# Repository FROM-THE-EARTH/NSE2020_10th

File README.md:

# NSE2020_10th
能代2020の10期ロケット用電装

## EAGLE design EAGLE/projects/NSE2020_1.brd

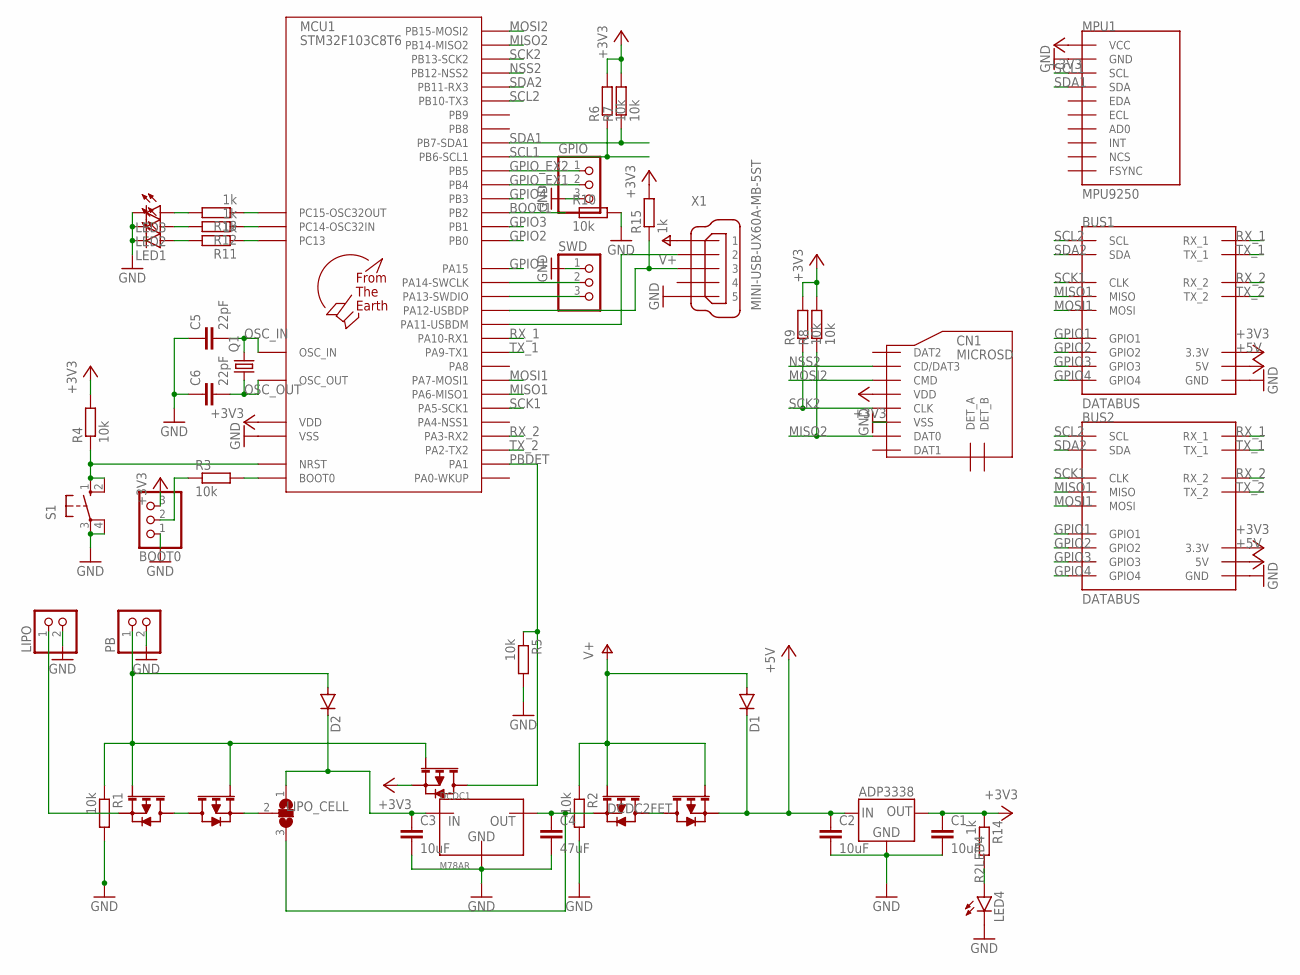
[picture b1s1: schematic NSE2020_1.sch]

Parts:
BOOT0: PINHD-1X3; 1X03
BUS1, BUS2: DATABUS; 8X2
C1, C2, C3: 10uF; C2012
C4: 47uF; C2012
C5, C6: 22pF; C2012
CN1: MICROSD; DM3AT
D1, D2: DIODE-SOD123; SOD123
DCDC1: M78AR
FET1, FET2, FET3, FET4, FET5: 2SJ681
GPIO: PINHD-1X3; 1X03
IC1: ADP3338-3.3; SOT-223
LED1, LED2, LED3, LED4: LEDSML0805; SML0805
LIPO: PINHD-1X2; 1X02
LIPO_CELL: SJ2W; SJ_2
MCU1: STM32F103C8T6; LQFP48
MPU1: MPU9250; GY-9250
PB: PINHD-1X2; 1X02
Q1: CRYSTALHC49S; HC49/S
R1, R2, R3, R4, R5, R6, R7, R8, R9, R10: 10k; M2012
R11, R12, R13, R14, R15: 1k; M2012
S1: 10-XX; B3F-10XX
SWD: PINHD-1X3; 1X03
U$1: F.T.E.LOGO; LOGO
X1: MINI-USB-UX60A-MB-5ST; UX60A-MB-5ST

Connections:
+3V3: BOOT0.3, BUS1.P6 (3.3V), BUS2.P6 (3.3V), C1.1, CN1.VDD, FET5.P$3, IC1.1 (OUT), IC1.2 (OUT), MCU1.1 (VDD), MCU1.9 (VDD), MCU1.24 (VDD), MCU1.36 (VDD), MCU1.48 (VDD), MPU1.P1 (VCC), R4.2, R6.2, R7.2, R8.2, R9.2, R14.1, R15.2
+5V: BUS1.P7 (5V), BUS2.P7 (5V), C2.1, D1.C, FET4.P$3, IC1.3 (IN)
BAT2DCDC: C3.1, D2.C, DCDC1.P1 (IN), LIPO_CELL.1
BOOT0: BOOT0.2, R3.1
BOOT0_R: MCU1.44 (BOOT0), R3.2
BOOT1: MCU1.20 (PB2), R10.1
DCDC2FET: C4.1, DCDC1.P3 (OUT), FET3.P$3, LIPO_CELL.3
DM: MCU1.32 (PA11-USBDM), X1.2
DP: MCU1.33 (PA12-USBDP), R15.1, X1.3
FET2FET: FET3.P$2, FET3.P$4, FET4.P$2, FET4.P$4
FET2JUMP: FET2.P$3, LIPO_CELL.2
GND: BOOT0.1, BUS1.P11 (GND), BUS2.P11 (GND), C1.2, C2.2, C3.2, C4.2, C5.1, C6.1, CN1.VSS, DCDC1.P2 (GND), GPIO.3, IC1.4 (GND), LED1.C, LED2.C, LED3.C, LED4.C, LIPO.2, MCU1.8 (VSS), MCU1.23 (VSS), MCU1.35 (VSS), MCU1.47 (VSS), MPU1.P2 (GND), PB.2, R1.2, R2.2, R5.2, R10.2, S1.3, S1.4 (P1), SWD.1, X1.5
GPIO1: BUS1.P3 (GPIO1), BUS2.P3 (GPIO1), MCU1.38 (PA15)
GPIO2: BUS1.P10 (GPIO2), BUS2.P10 (GPIO2), MCU1.18 (PB0)
GPIO3: BUS1.P14 (GPIO3), BUS2.P14 (GPIO3), MCU1.19 (PB1)
GPIO4: BUS1.P15 (GPIO4), BUS2.P15 (GPIO4), MCU1.39 (PB3)
GPIO_EX1: GPIO.2, MCU1.40 (PB4)
GPIO_EX2: GPIO.1, MCU1.41 (PB5)
IO2R1: MCU1.2 (PC13), R11.1
IO2R2: MCU1.3 (PC14-OSC32IN), R12.1
IO2R3: MCU1.4 (PC15-OSC32OUT), R13.1
LIPOIN: FET1.P$3, LIPO.1
LIPO_FET2FET: FET1.P$2, FET1.P$4, FET2.P$2, FET2.P$4
MISO1: BUS1.P12 (MISO), BUS2.P12 (MISO), MCU1.16 (PA6-MISO1)
MISO2: CN1.DAT0, MCU1.27 (PB14-MISO2), R8.1
MOSI1: BUS1.P2 (MOSI), BUS2.P2 (MOSI), MCU1.17 (PA7-MOSI1)
MOSI2: CN1.CMD, MCU1.28 (PB15-MOSI2)
NRST: MCU1.7 (NRST), R4.1, S1.1 (S), S1.2 (S1)
NSS2: CN1.CD/DAT3, MCU1.25 (PB12-NSS2)
OSC_IN: C5.2, MCU1.5 (OSC_IN), Q1.2
OSC_OUT: C6.2, MCU1.6 (OSC_OUT), Q1.1
PBDET: FET5.P$2, FET5.P$4, MCU1.11 (PA1), R5.1
PBIN: D2.A, FET1.P$1, FET2.P$1, FET5.P$1, PB.1, R1.1
R2LED1: LED1.A, R11.2
R2LED2: LED2.A, R12.2
R2LED3: LED3.A, R13.2
R2LED4: LED4.A, R14.2
RX_1: BUS1.P4 (RX_1), BUS2.P4 (RX_1), MCU1.31 (PA10-RX1)
RX_2: BUS1.P9 (RX_2), BUS2.P9 (RX_2), MCU1.13 (PA3-RX2)
SCK1: BUS1.P1 (CLK), BUS2.P1 (CLK), MCU1.15 (PA5-SCK1)
SCK2: CN1.CLK, MCU1.26 (PB13-SCK2), R9.1
SCL1: MCU1.42 (PB6-SCL1), MPU1.P3 (SCL), R6.1
SCL2: BUS1.P0 (SCL), BUS2.P0 (SCL), MCU1.21 (PB10-TX3)
SDA1: MCU1.43 (PB7-SDA1), MPU1.P4 (SDA), R7.1
SDA2: BUS1.P13 (SDA), BUS2.P13 (SDA), MCU1.22 (PB11-RX3)
SWCLK: MCU1.37 (PA14-SWCLK), SWD.2
SWDIO: MCU1.34 (PA13-SWDIO), SWD.3
TX_1: BUS1.P5 (TX_1), BUS2.P5 (TX_1), MCU1.30 (PA9-TX1)
TX_2: BUS1.P8 (TX_2), BUS2.P8 (TX_2), MCU1.12 (PA2-TX2)
V+: D1.A, FET3.P$1, FET4.P$1, R2.1, X1.1

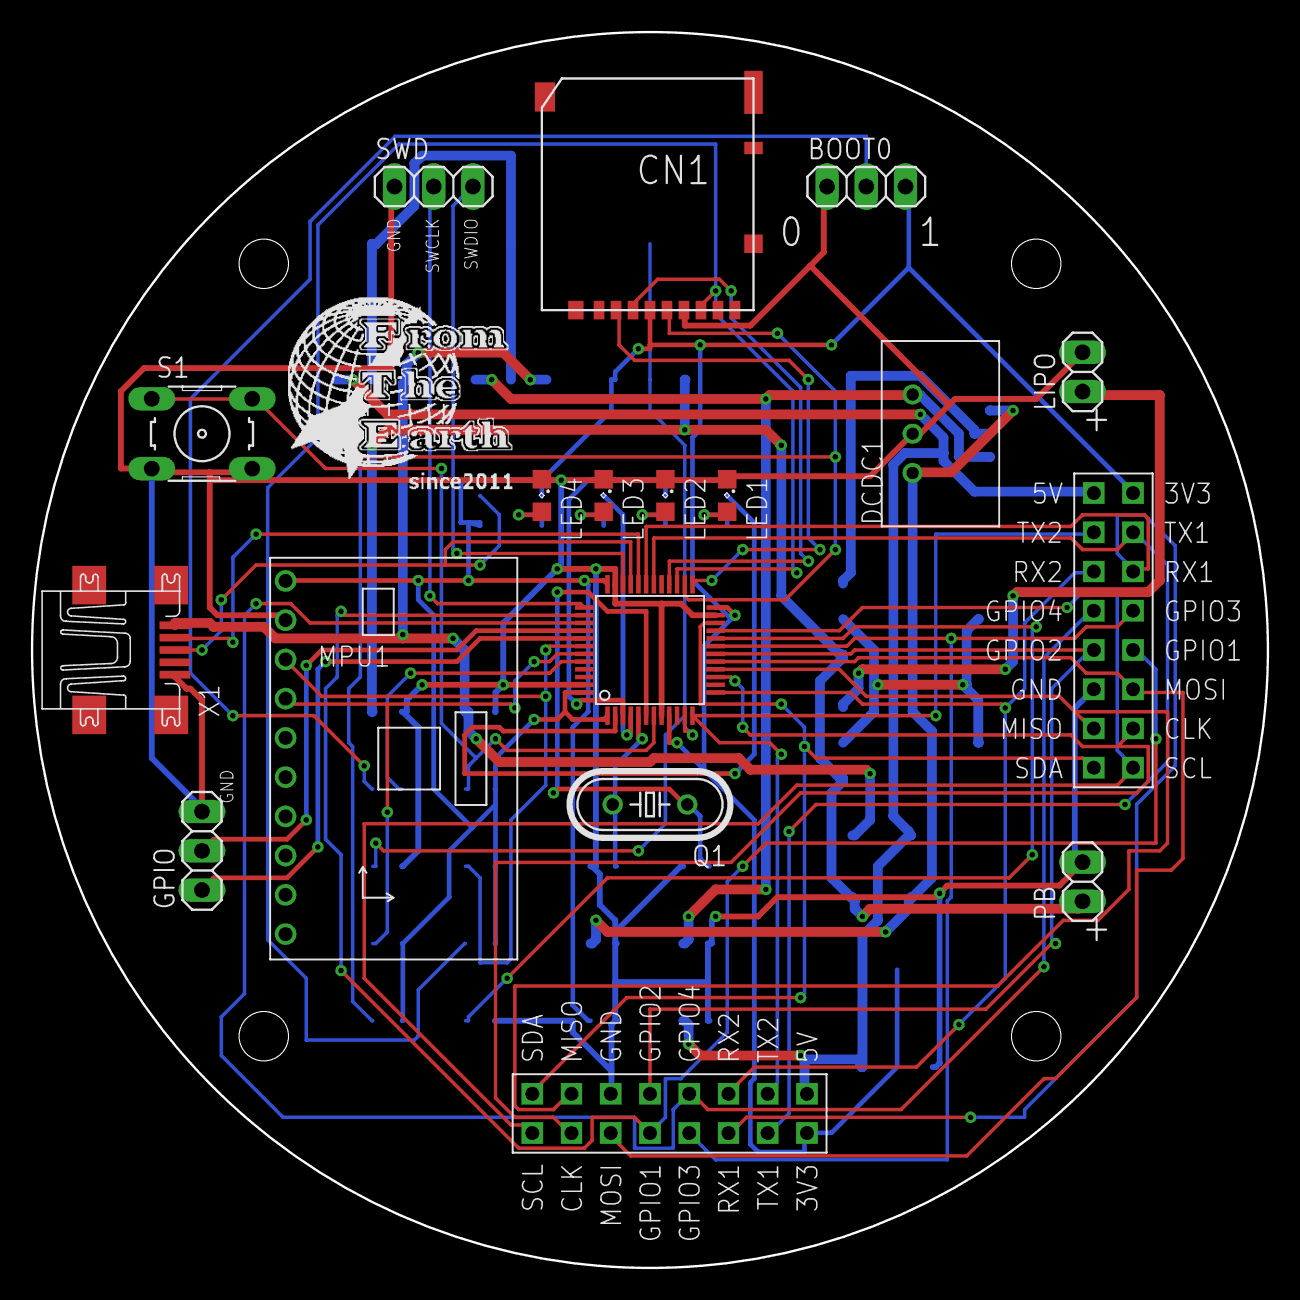
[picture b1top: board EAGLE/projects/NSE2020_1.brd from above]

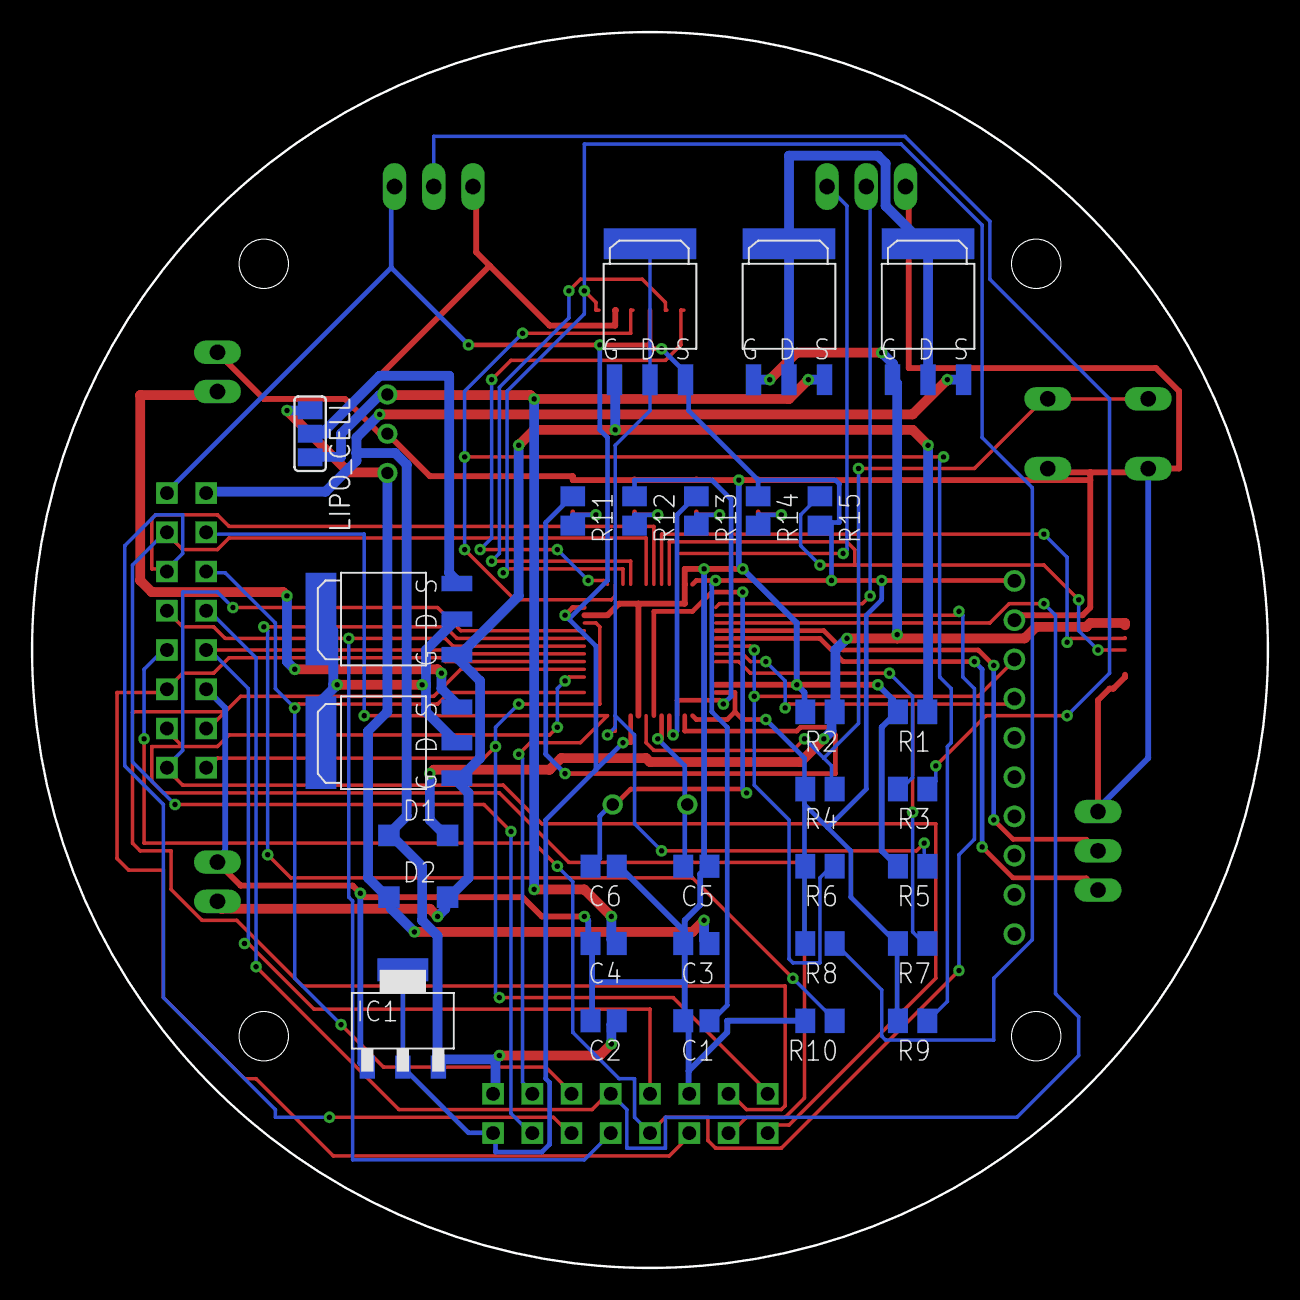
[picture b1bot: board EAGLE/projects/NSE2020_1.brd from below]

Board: 2 copper layers, 80.0 x 80.0 mm, 49 parts (30 on the bottom side), 50 nets.

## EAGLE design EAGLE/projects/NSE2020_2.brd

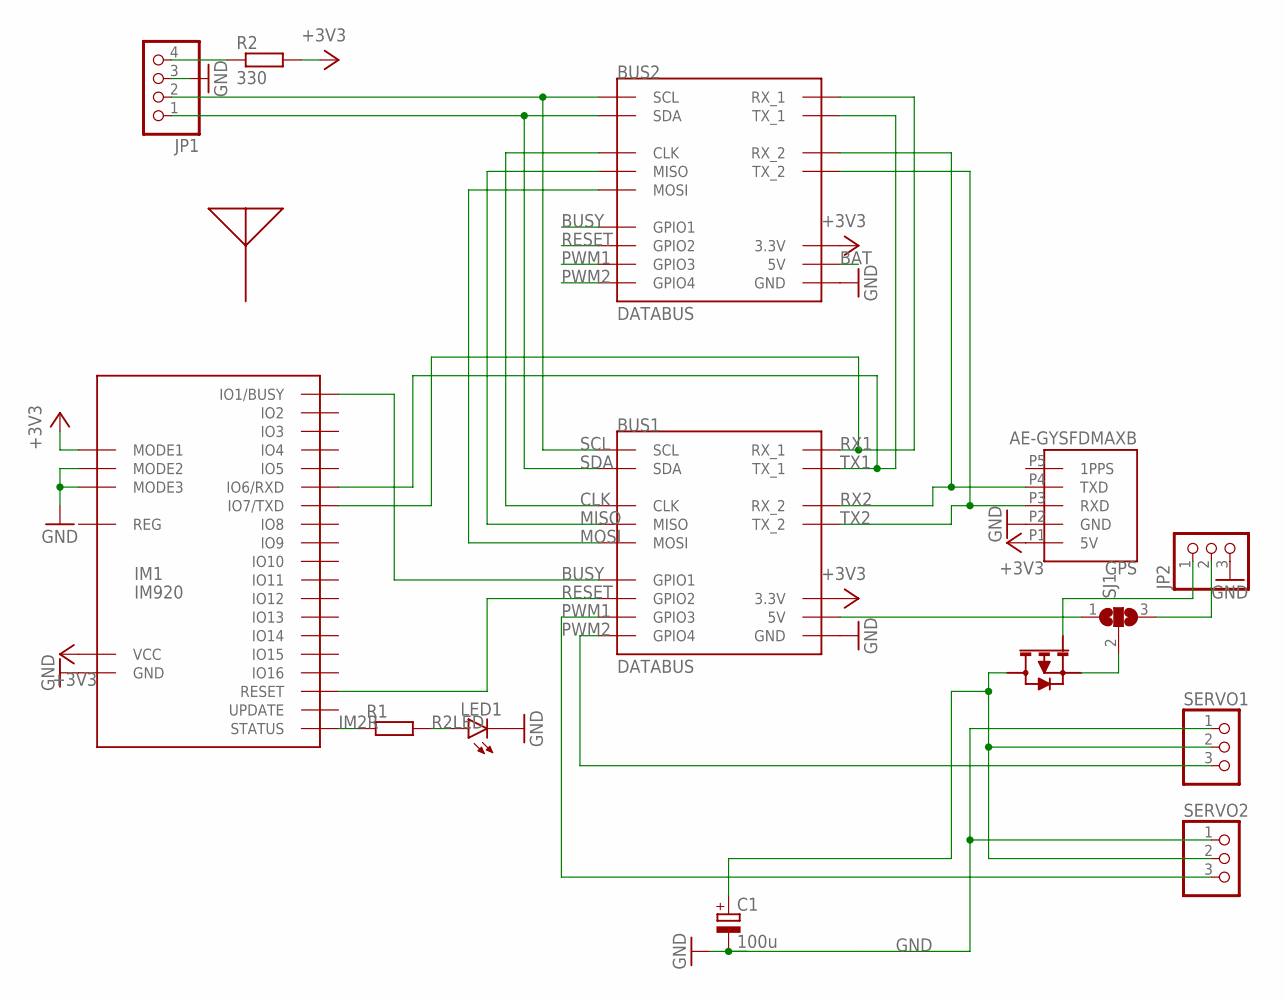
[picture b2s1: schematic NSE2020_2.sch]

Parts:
ANT1: IM920ANT-XS; ANTENNA
BUS1, BUS2: DATABUS; 8X2
C1: 100u; E2,5-6
GPS: AE-GYSFDMAXB
IM1: IM920
JP1: PINHD-1X4; 1X04
JP2: PINHD-1X3; 1X03
LED1: LEDSMT1206; 1206
R1: R-EU_M2012; M2012
R2: 330; R2012
SERVO1, SERVO2: PINHD-1X3; 1X03
SJ1: SJ2W; SJ_2
U$1: 2SJ681

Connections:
5V_CELL: BUS1.P7 (5V), SJ1.1
+3V3: BUS1.P6 (3.3V), BUS2.P6 (3.3V), GPS.P1 (5V), IM1.IO17 (MODE1), IM1.IO23 (VCC), R2.2
BAT: BUS2.P7 (5V), C1.+, SERVO1.2, SERVO2.2, U$1.P$2, U$1.P$4
BAT_CELL: JP2.2, SJ1.3
BUSY: BUS1.P3 (GPIO1), BUS2.P3 (GPIO1), IM1.IO1 (IO1/BUSY)
CLK: BUS1.P1 (CLK), BUS2.P1 (CLK)
GND: BUS1.P11 (GND), BUS2.P11 (GND), C1.-, GPS.P2 (GND), IM1.IO18 (MODE2), IM1.IO19 (MODE3), IM1.IO24 (GND), JP1.3, JP2.3, LED1.C, SERVO1.1, SERVO2.1
IM2R: IM1.IO21 (STATUS), R1.1
MISO: BUS1.P12 (MISO), BUS2.P12 (MISO)
MOSI: BUS1.P2 (MOSI), BUS2.P2 (MOSI)
unnamed: SJ1.2, U$1.P$3
unnamed: JP2.1, U$1.P$1
PWM1: BUS1.P14 (GPIO3), BUS2.P14 (GPIO3), SERVO2.3
PWM2: BUS1.P15 (GPIO4), BUS2.P15 (GPIO4), SERVO1.3
R2BMP: JP1.4, R2.1
R2LED: LED1.A, R1.2
RESET: BUS1.P10 (GPIO2), BUS2.P10 (GPIO2), IM1.IO25 (RESET)
RX1: BUS1.P4 (RX_1), BUS2.P4 (RX_1), IM1.IO7 (IO7/TXD)
RX2: BUS1.P9 (RX_2), BUS2.P9 (RX_2), GPS.P4 (TXD)
SCL: BUS1.P0 (SCL), BUS2.P0 (SCL), JP1.2
SDA: BUS1.P13 (SDA), BUS2.P13 (SDA), JP1.1
TX1: BUS1.P5 (TX_1), BUS2.P5 (TX_1), IM1.IO6 (IO6/RXD)
TX2: BUS1.P8 (TX_2), BUS2.P8 (TX_2), GPS.P3 (RXD)

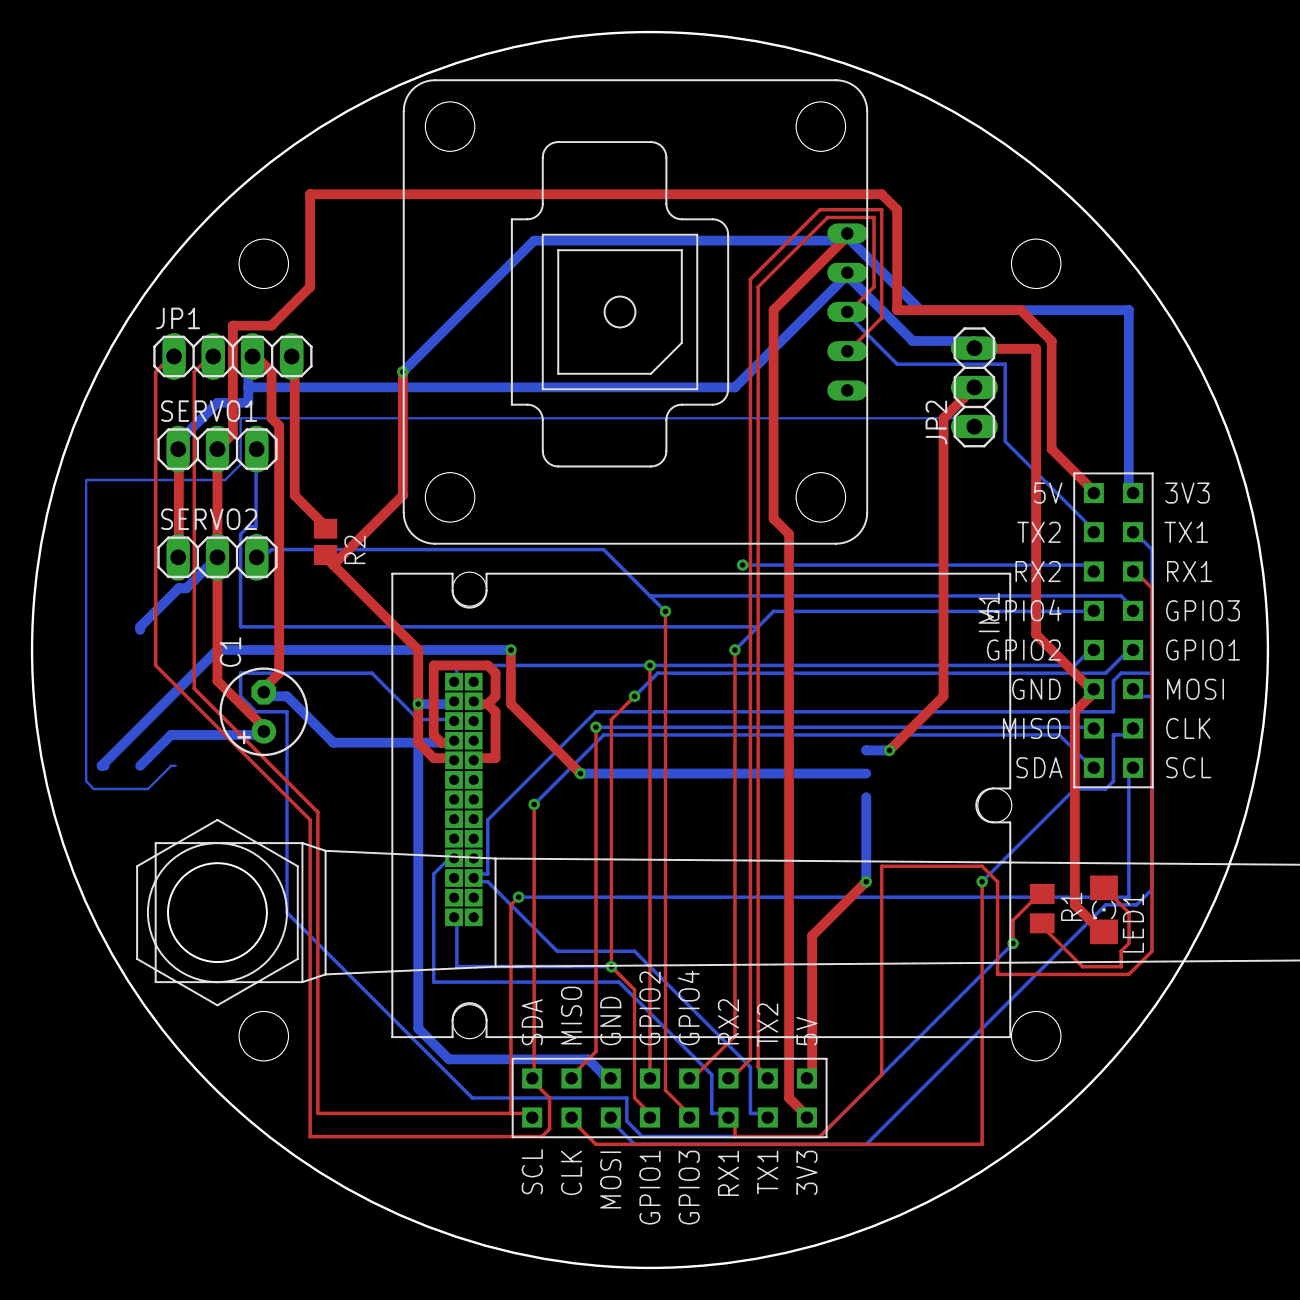
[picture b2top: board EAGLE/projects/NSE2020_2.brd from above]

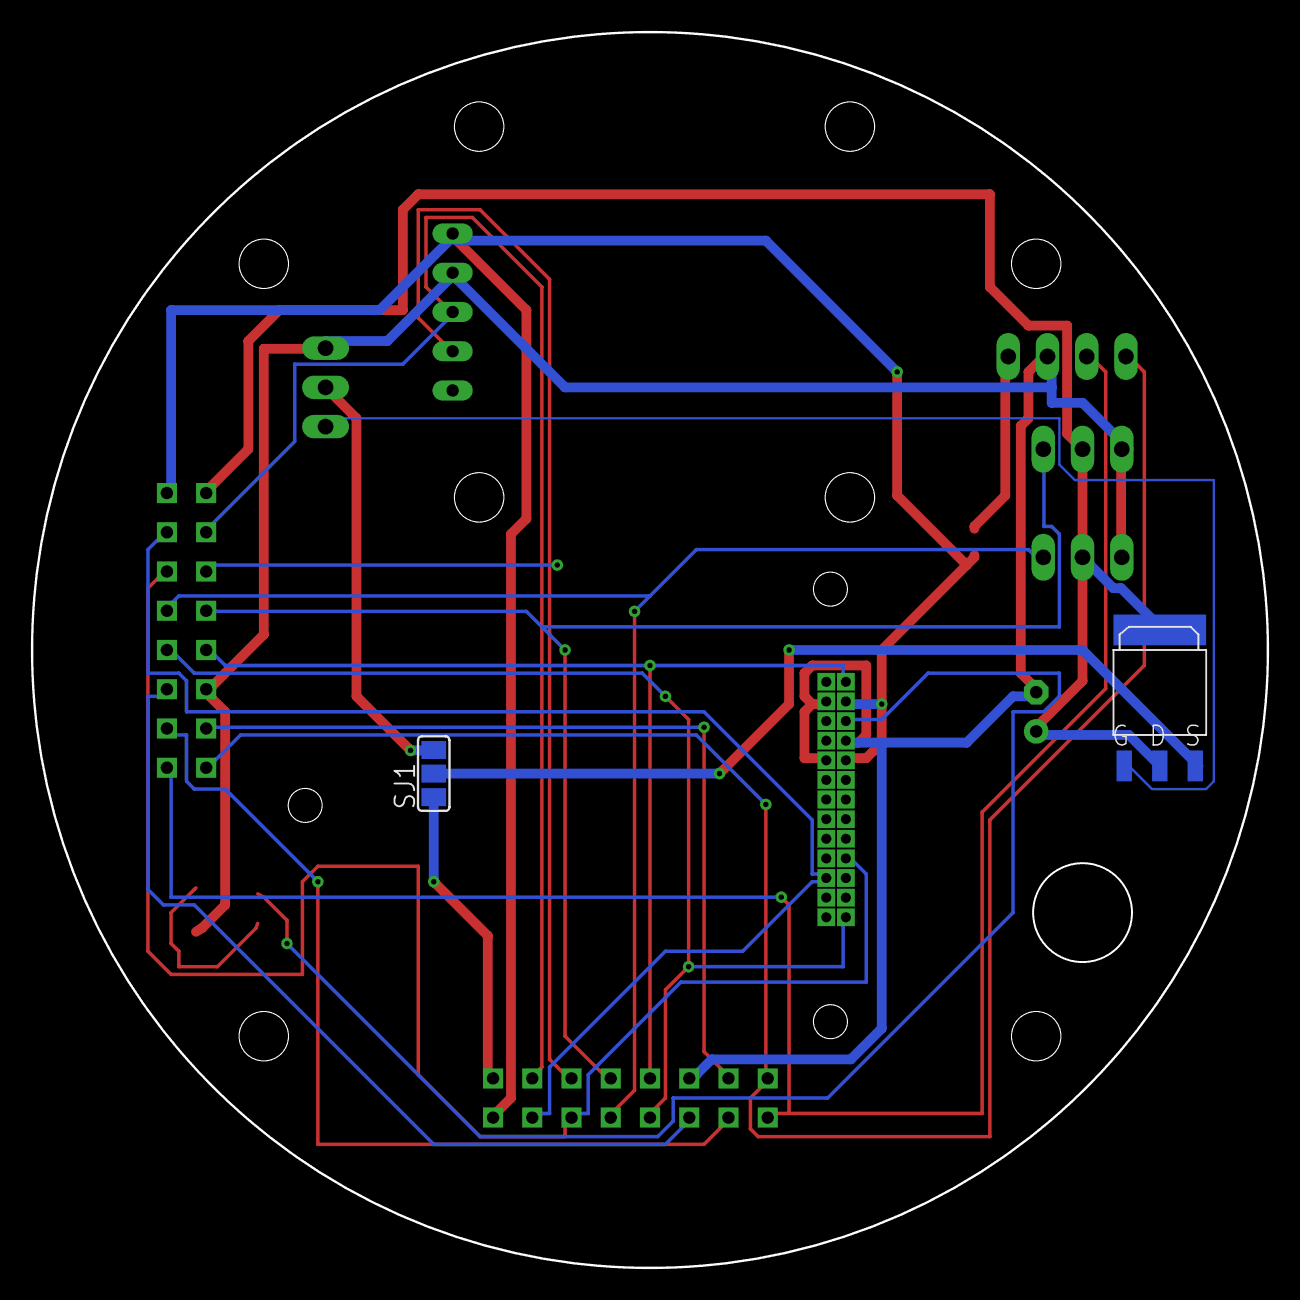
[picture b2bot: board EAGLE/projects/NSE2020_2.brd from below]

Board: 2 copper layers, 80.0 x 80.0 mm, 15 parts (2 on the bottom side), 23 nets.

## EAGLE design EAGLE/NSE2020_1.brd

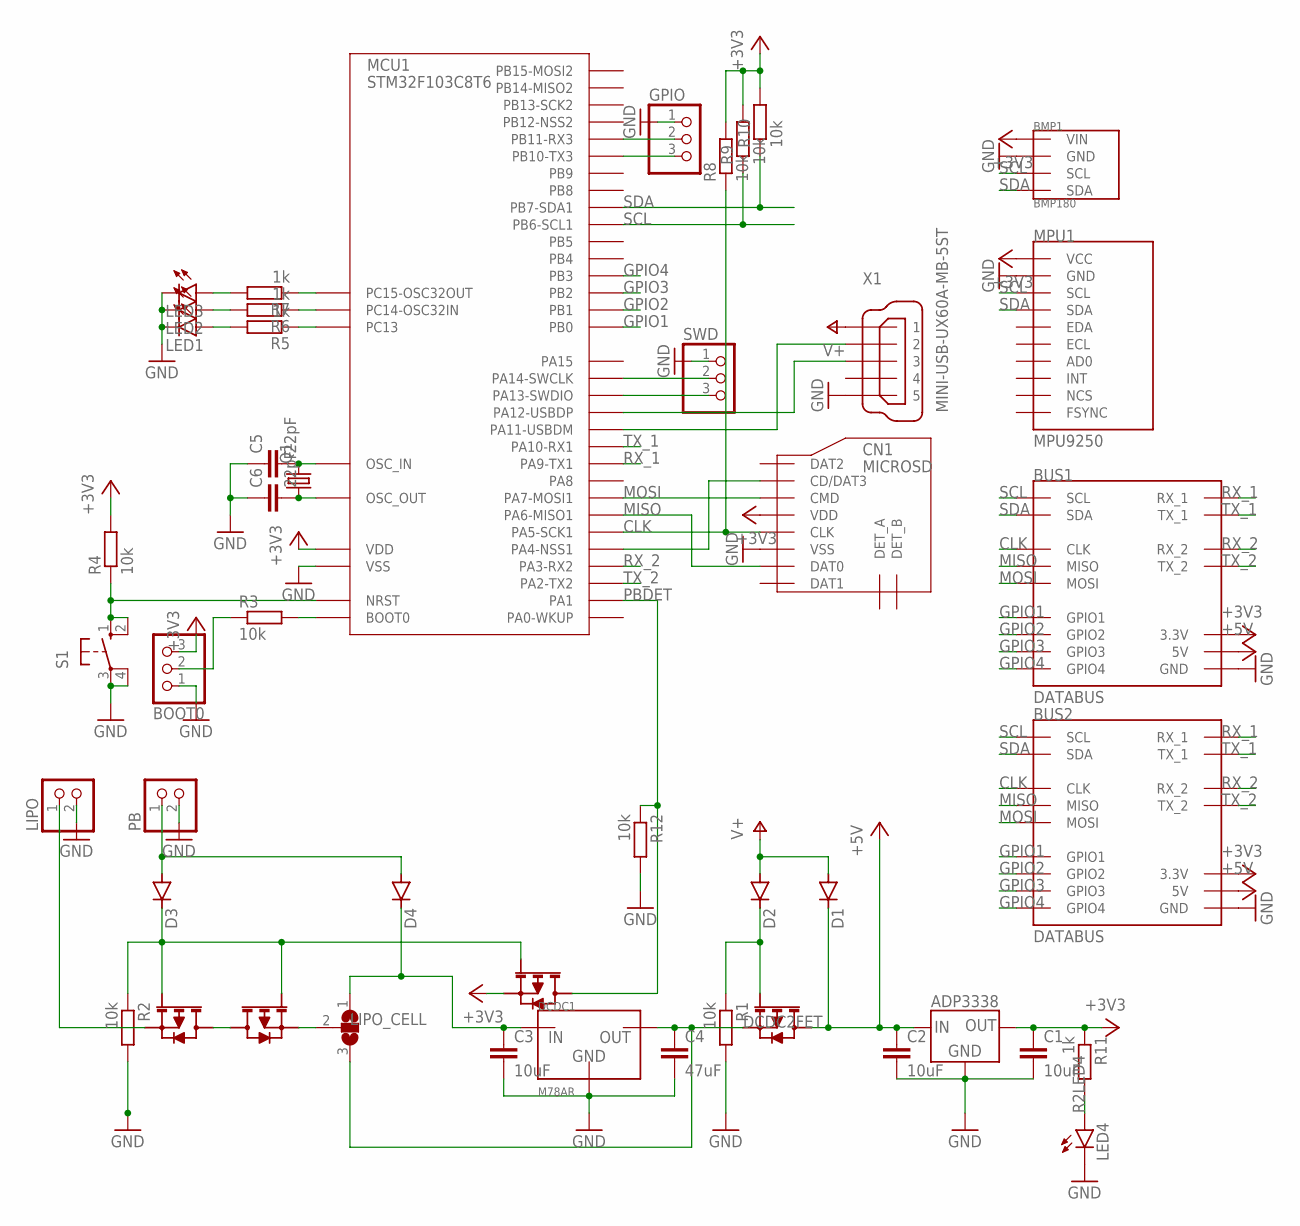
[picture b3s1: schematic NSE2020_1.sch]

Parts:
BMP1: BMP180; GY-68
BOOT0: PINHD-1X3; 1X03
BUS1, BUS2: DATABUS; 8X2
C1, C2, C3: 10uF; C2012
C4: 47uF; C2012
C5, C6: 22pF; C2012
CN1: MICROSD; DM3AT
D1, D2, D3, D4: DIODE-SOD123; SOD123
DCDC1: M78AR
GPIO: PINHD-1X3; 1X03
IC1: ADP3338-3.3; SOT-223
LED1, LED2, LED3, LED4: LEDSMT1206; 1206
LIPO: PINHD-1X2; 1X02
LIPO_CELL: SJ2W; SJ_2
MCU1: STM32F103C8T6; LQFP48
MPU1: MPU9250; GY-9250
PB: PINHD-1X2; 1X02
Q1: CRYSTALHC49S; HC49/S
R1, R2, R3, R4, R8, R9, R10, R12: 10k; M2012
R5, R6, R7, R11: 1k; M2012
S1: 10-XX; B3F-10XX
SWD: PINHD-1X3; 1X03
U$1, U$2, U$3, U$4: 2SJ681
X1: MINI-USB-UX60A-MB-5ST; UX60A-MB-5ST

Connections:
+3V3: BMP1.P1 (VIN), BOOT0.3, BUS1.P6 (3.3V), BUS2.P6 (3.3V), C1.1, CN1.VDD, IC1.1 (OUT), IC1.2 (OUT), MCU1.1 (VDD), MCU1.9 (VDD), MCU1.24 (VDD), MCU1.36 (VDD), MCU1.48 (VDD), MPU1.P1 (VCC), R4.2, R8.2, R9.2, R10.2, R11.1, U$4.P$3
+5V: BUS1.P7 (5V), BUS2.P7 (5V), C2.1, D1.C, IC1.3 (IN), U$1.P$2, U$1.P$4
BAT2DCDC: C3.1, D4.C, DCDC1.P1 (IN), LIPO_CELL.1
BOOT0: BOOT0.2, R3.1
BOOT0_R: MCU1.44 (BOOT0), R3.2
CLK: BUS1.P1 (CLK), BUS2.P1 (CLK), CN1.CLK, MCU1.15 (PA5-SCK1), R8.1
CRYIN: C5.2, MCU1.5 (OSC_IN), Q1.2
CRYOUT: C6.2, MCU1.6 (OSC_OUT), Q1.1
CS_SD: CN1.CD/DAT3, MCU1.14 (PA4-NSS1)
DCDC2FET: C4.1, DCDC1.P3 (OUT), LIPO_CELL.3, U$1.P$3
DM: MCU1.32 (PA11-USBDM), X1.2
DP: MCU1.33 (PA12-USBDP), X1.3
FET2JUMP: LIPO_CELL.2, U$2.P$3
GND: BMP1.P2 (GND), BOOT0.1, BUS1.P11 (GND), BUS2.P11 (GND), C1.2, C2.2, C3.2, C4.2, C5.1, C6.1, CN1.VSS, DCDC1.P2 (GND), GPIO.1, IC1.4 (GND), LED1.C, LED2.C, LED3.C, LED4.C, LIPO.2, MCU1.8 (VSS), MCU1.23 (VSS), MCU1.35 (VSS), MCU1.47 (VSS), MPU1.P10 (GND), PB.2, R1.2, R2.2, R12.2, S1.3, S1.4 (P1), SWD.1, X1.5
GPIO1: BUS1.P3 (GPIO1), BUS2.P3 (GPIO1), MCU1.18 (PB0)
GPIO2: BUS1.P10 (GPIO2), BUS2.P10 (GPIO2), MCU1.19 (PB1)
GPIO3: BUS1.P14 (GPIO3), BUS2.P14 (GPIO3), MCU1.20 (PB2)
GPIO4: BUS1.P15 (GPIO4), BUS2.P15 (GPIO4), MCU1.39 (PB3)
IO2LED1: MCU1.2 (PC13), R5.1
IO2R2: MCU1.3 (PC14-OSC32IN), R6.1
IO2R3: MCU1.4 (PC15-OSC32OUT), R7.1
LIPOIN: LIPO.1, U$3.P$3
LIPO_FET2FET: U$2.P$2, U$2.P$4, U$3.P$2, U$3.P$4
MISO: BUS1.P12 (MISO), BUS2.P12 (MISO), CN1.DAT0, MCU1.16 (PA6-MISO1)
MOSI: BUS1.P2 (MOSI), BUS2.P2 (MOSI), CN1.CMD, MCU1.17 (PA7-MOSI1)
NRST: MCU1.7 (NRST), R4.1, S1.1 (S), S1.2 (S1)
PBDET: MCU1.11 (PA1), R12.1, U$4.P$2, U$4.P$4
PBGATE: D3.C, R2.1, U$2.P$1, U$3.P$1, U$4.P$1
PBIN: D3.A, D4.A, PB.1
R2LED1: LED1.A, R5.2
R2LED2: LED2.A, R6.2
R2LED3: LED3.A, R7.2
R2LED4: LED4.A, R11.2
RX_1: BUS1.P4 (RX_1), BUS2.P4 (RX_1), MCU1.30 (PA9-TX1)
RX_2: BUS1.P9 (RX_2), BUS2.P9 (RX_2), MCU1.13 (PA3-RX2)
RX_3: GPIO.2, MCU1.22 (PB11-RX3)
SCL: BMP1.P3 (SCL), BUS1.P0 (SCL), BUS2.P0 (SCL), MCU1.42 (PB6-SCL1), MPU1.P3 (SCL), R9.1
SDA: BMP1.P4 (SDA), BUS1.P13 (SDA), BUS2.P13 (SDA), MCU1.43 (PB7-SDA1), MPU1.P4 (SDA), R10.1
SWCLK: MCU1.37 (PA14-SWCLK), SWD.2
SWDIO: MCU1.34 (PA13-SWDIO), SWD.3
TX_1: BUS1.P5 (TX_1), BUS2.P5 (TX_1), MCU1.31 (PA10-RX1)
TX_2: BUS1.P8 (TX_2), BUS2.P8 (TX_2), MCU1.12 (PA2-TX2)
TX_3: GPIO.3, MCU1.21 (PB10-TX3)
USBGATE: D2.C, R1.1, U$1.P$1
V+: D1.A, D2.A, X1.1

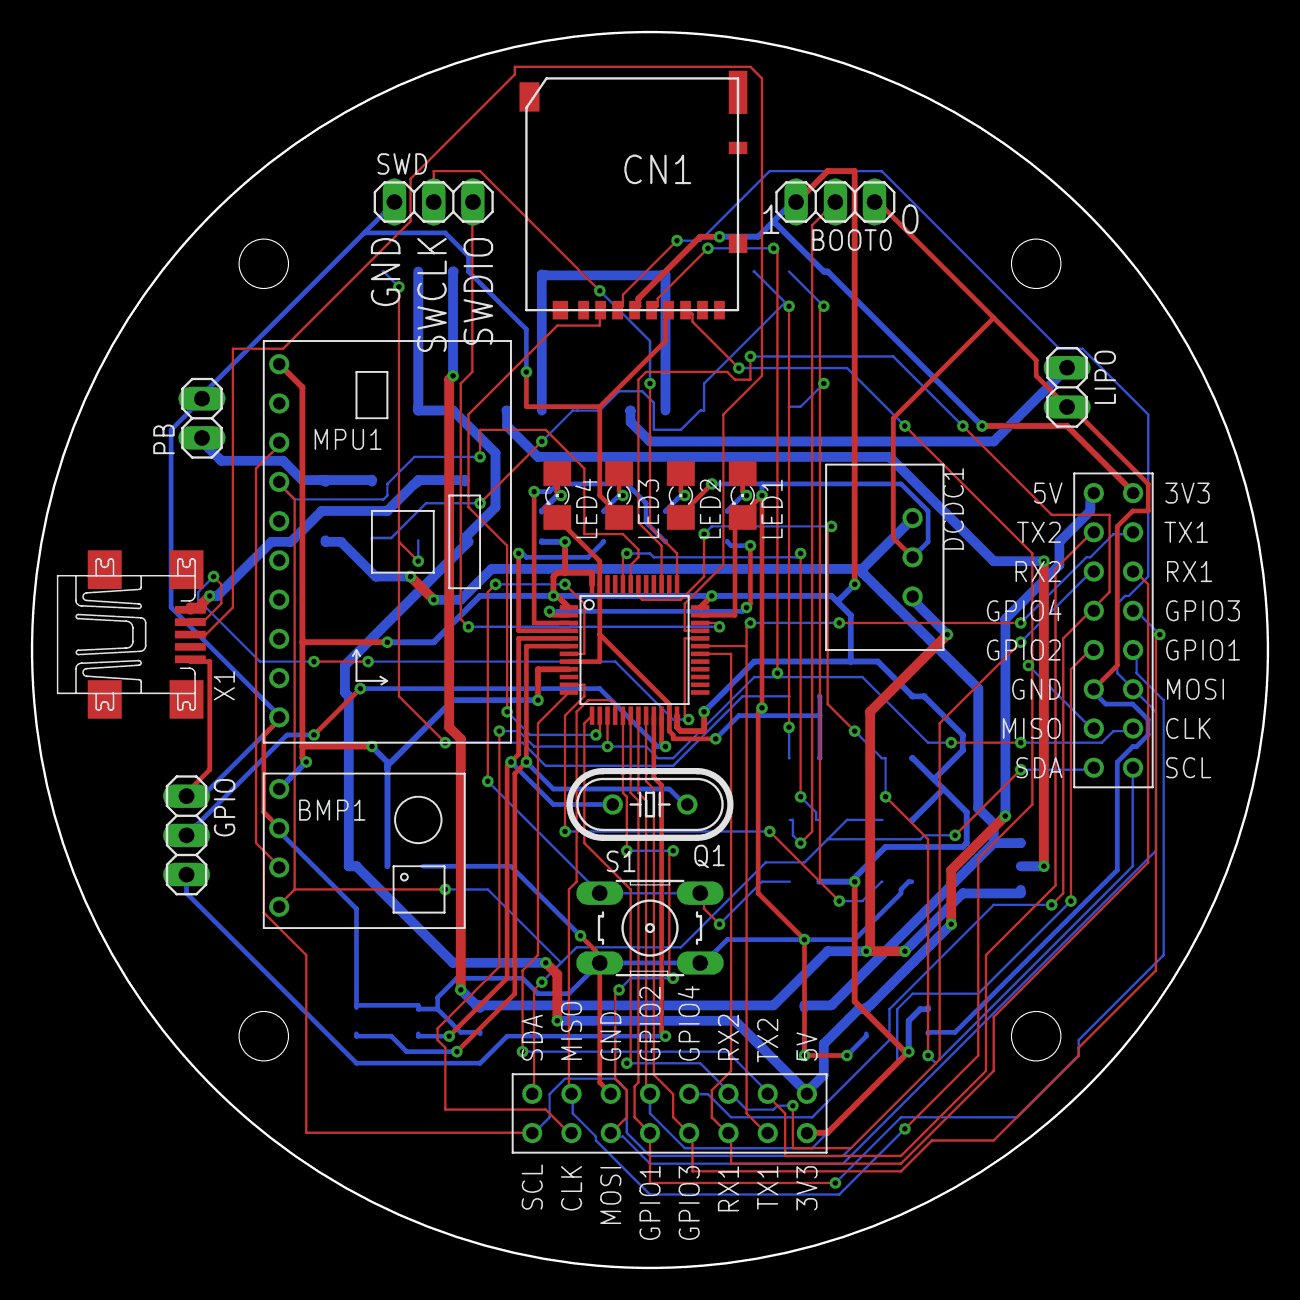
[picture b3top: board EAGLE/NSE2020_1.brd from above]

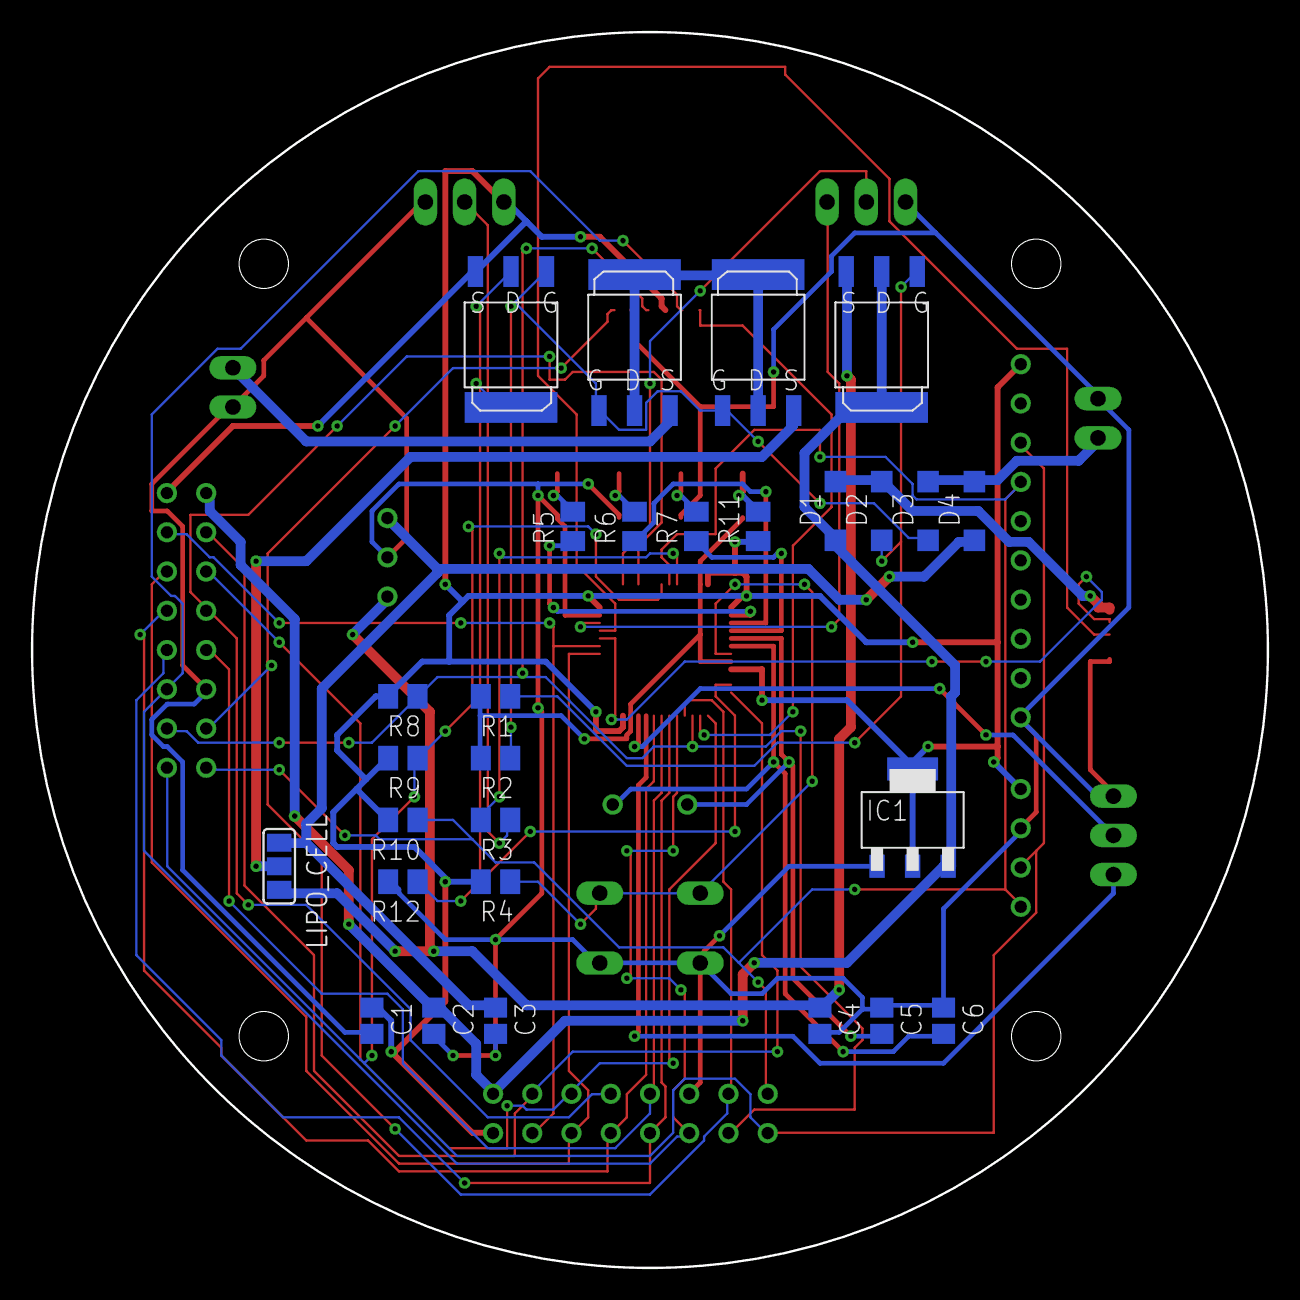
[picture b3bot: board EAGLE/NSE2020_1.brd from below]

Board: 2 copper layers, 80.0 x 80.0 mm, 47 parts (28 on the bottom side), 45 nets.

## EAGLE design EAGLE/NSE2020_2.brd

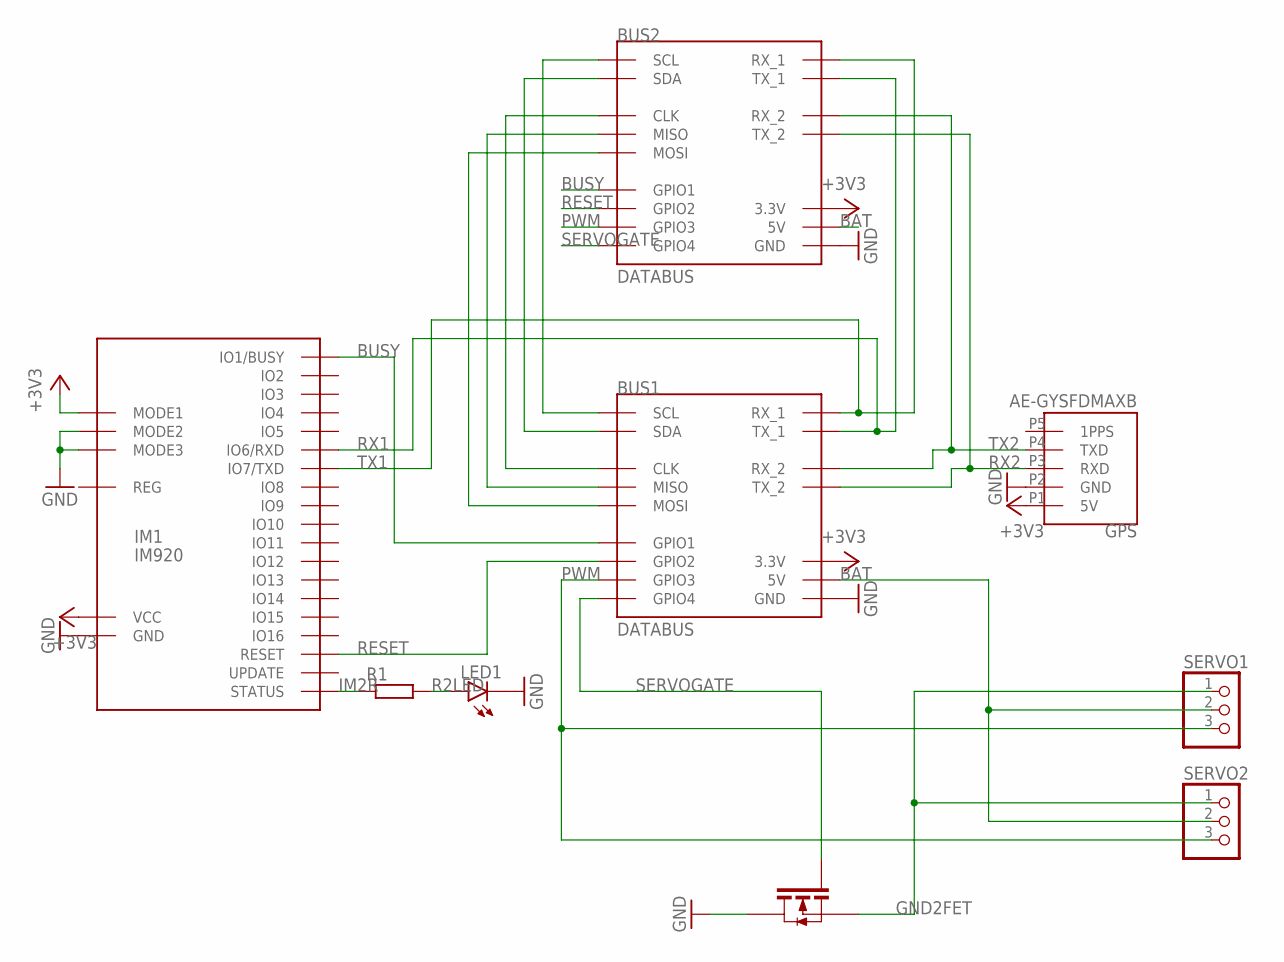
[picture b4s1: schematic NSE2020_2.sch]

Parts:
BUS1, BUS2: DATABUS; 8X2
FET1: 2SK4033
GPS: AE-GYSFDMAXB
IM1: IM920
LED1: LEDSMT1206; 1206
R1: R-EU_M2012; M2012
SERVO1, SERVO2: PINHD-1X3; 1X03

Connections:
+3V3: BUS1.P6 (3.3V), BUS2.P6 (3.3V), GPS.P1 (5V), IM1.IO2 (VCC), IM1.IO5 (MODE1)
BAT: BUS1.P7 (5V), BUS2.P7 (5V), SERVO1.2, SERVO2.2
BUSY: BUS1.P3 (GPIO1), BUS2.P3 (GPIO1), IM1.IO13 (IO1/BUSY)
GND: BUS1.P11 (GND), BUS2.P11 (GND), FET1.P$1 (D), FET1.P$2 (D), GPS.P2 (GND), IM1.IO4 (MODE3), IM1.IO22 (MODE2), IM1.IO25 (GND), LED1.C
GND2FET: FET1.P$4 (S), SERVO1.1, SERVO2.1
IM2R: IM1.IO3 (STATUS), R1.1
unnamed: BUS1.P0 (SCL), BUS2.P0 (SCL)
unnamed: BUS1.P13 (SDA), BUS2.P13 (SDA)
unnamed: BUS1.P1 (CLK), BUS2.P1 (CLK)
unnamed: BUS1.P12 (MISO), BUS2.P12 (MISO)
unnamed: BUS1.P2 (MOSI), BUS2.P2 (MOSI)
PWM: BUS1.P14 (GPIO3), BUS2.P14 (GPIO3), SERVO1.3, SERVO2.3
R2LED: LED1.A, R1.2
RESET: BUS1.P10 (GPIO2), BUS2.P10 (GPIO2), IM1.IO1 (RESET)
RX1: BUS1.P5 (TX_1), BUS2.P5 (TX_1), IM1.IO16 (IO6/RXD)
RX2: BUS1.P8 (TX_2), BUS2.P8 (TX_2), GPS.P3 (RXD)
SERVOGATE: BUS1.P15 (GPIO4), BUS2.P15 (GPIO4), FET1.P$3 (G)
TX1: BUS1.P4 (RX_1), BUS2.P4 (RX_1), IM1.IO10 (IO7/TXD)
TX2: BUS1.P9 (RX_2), BUS2.P9 (RX_2), GPS.P4 (TXD)

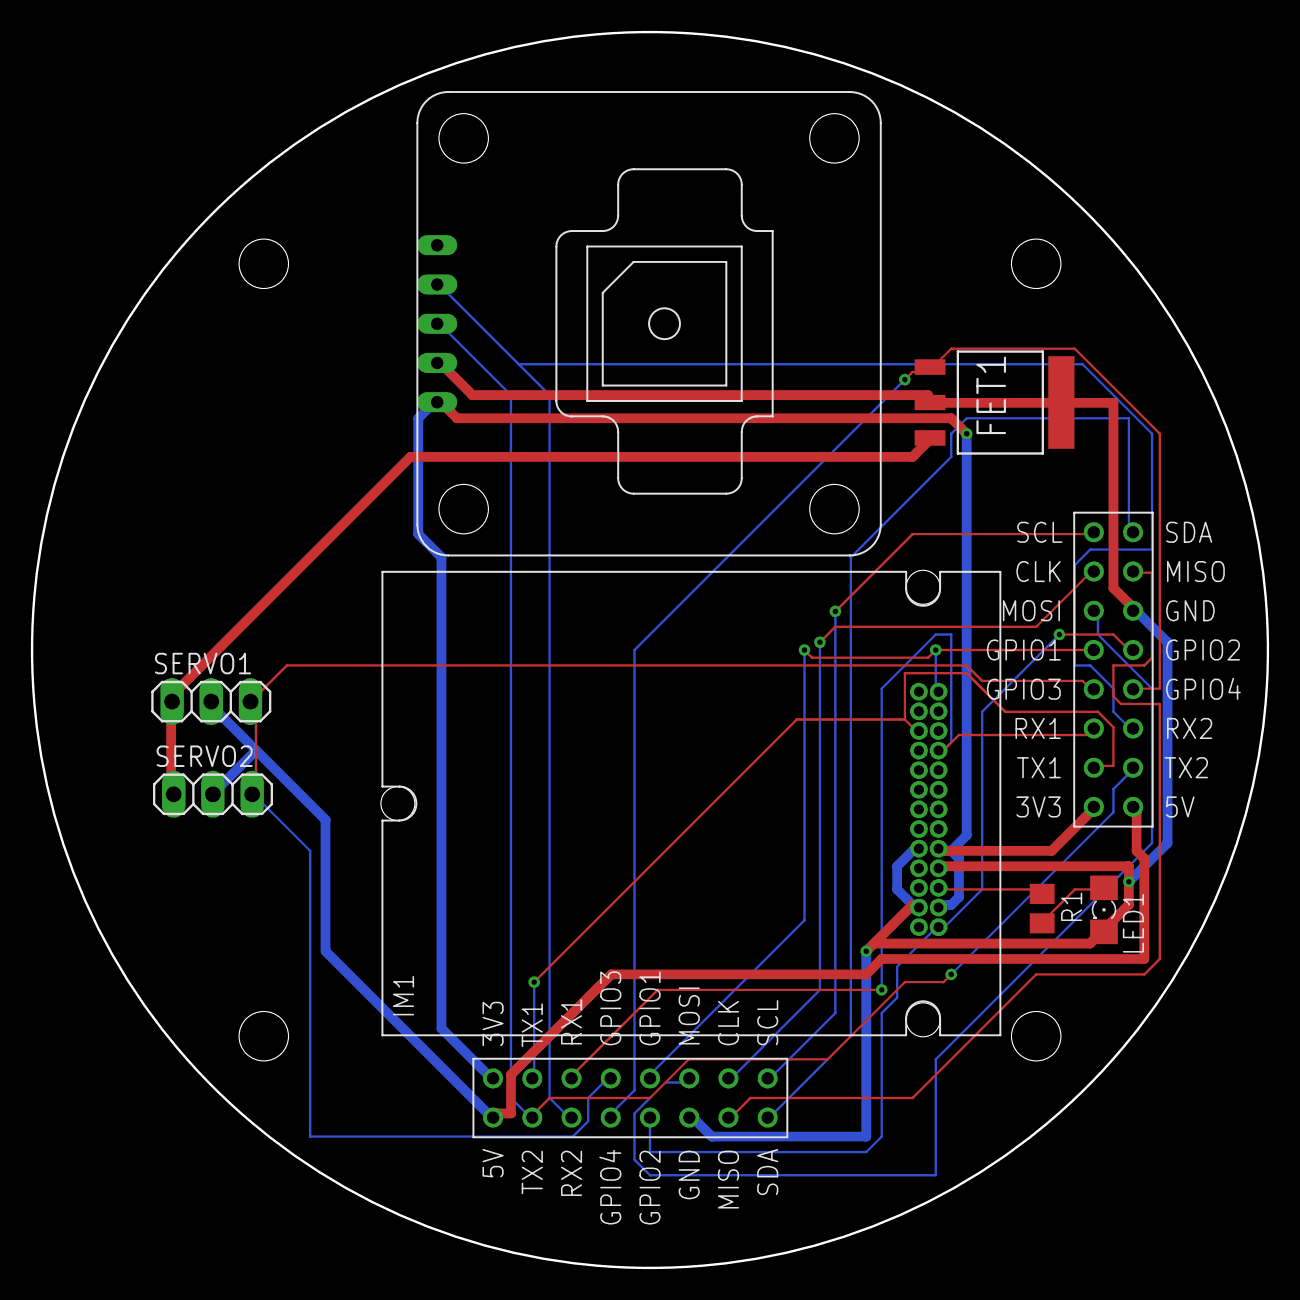
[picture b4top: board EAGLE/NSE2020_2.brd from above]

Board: 2 copper layers, 80.0 x 80.0 mm, 9 parts (0 on the bottom side), 19 nets.
